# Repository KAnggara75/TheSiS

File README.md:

# TheSiS

My TheSiS for Bachelor Degree

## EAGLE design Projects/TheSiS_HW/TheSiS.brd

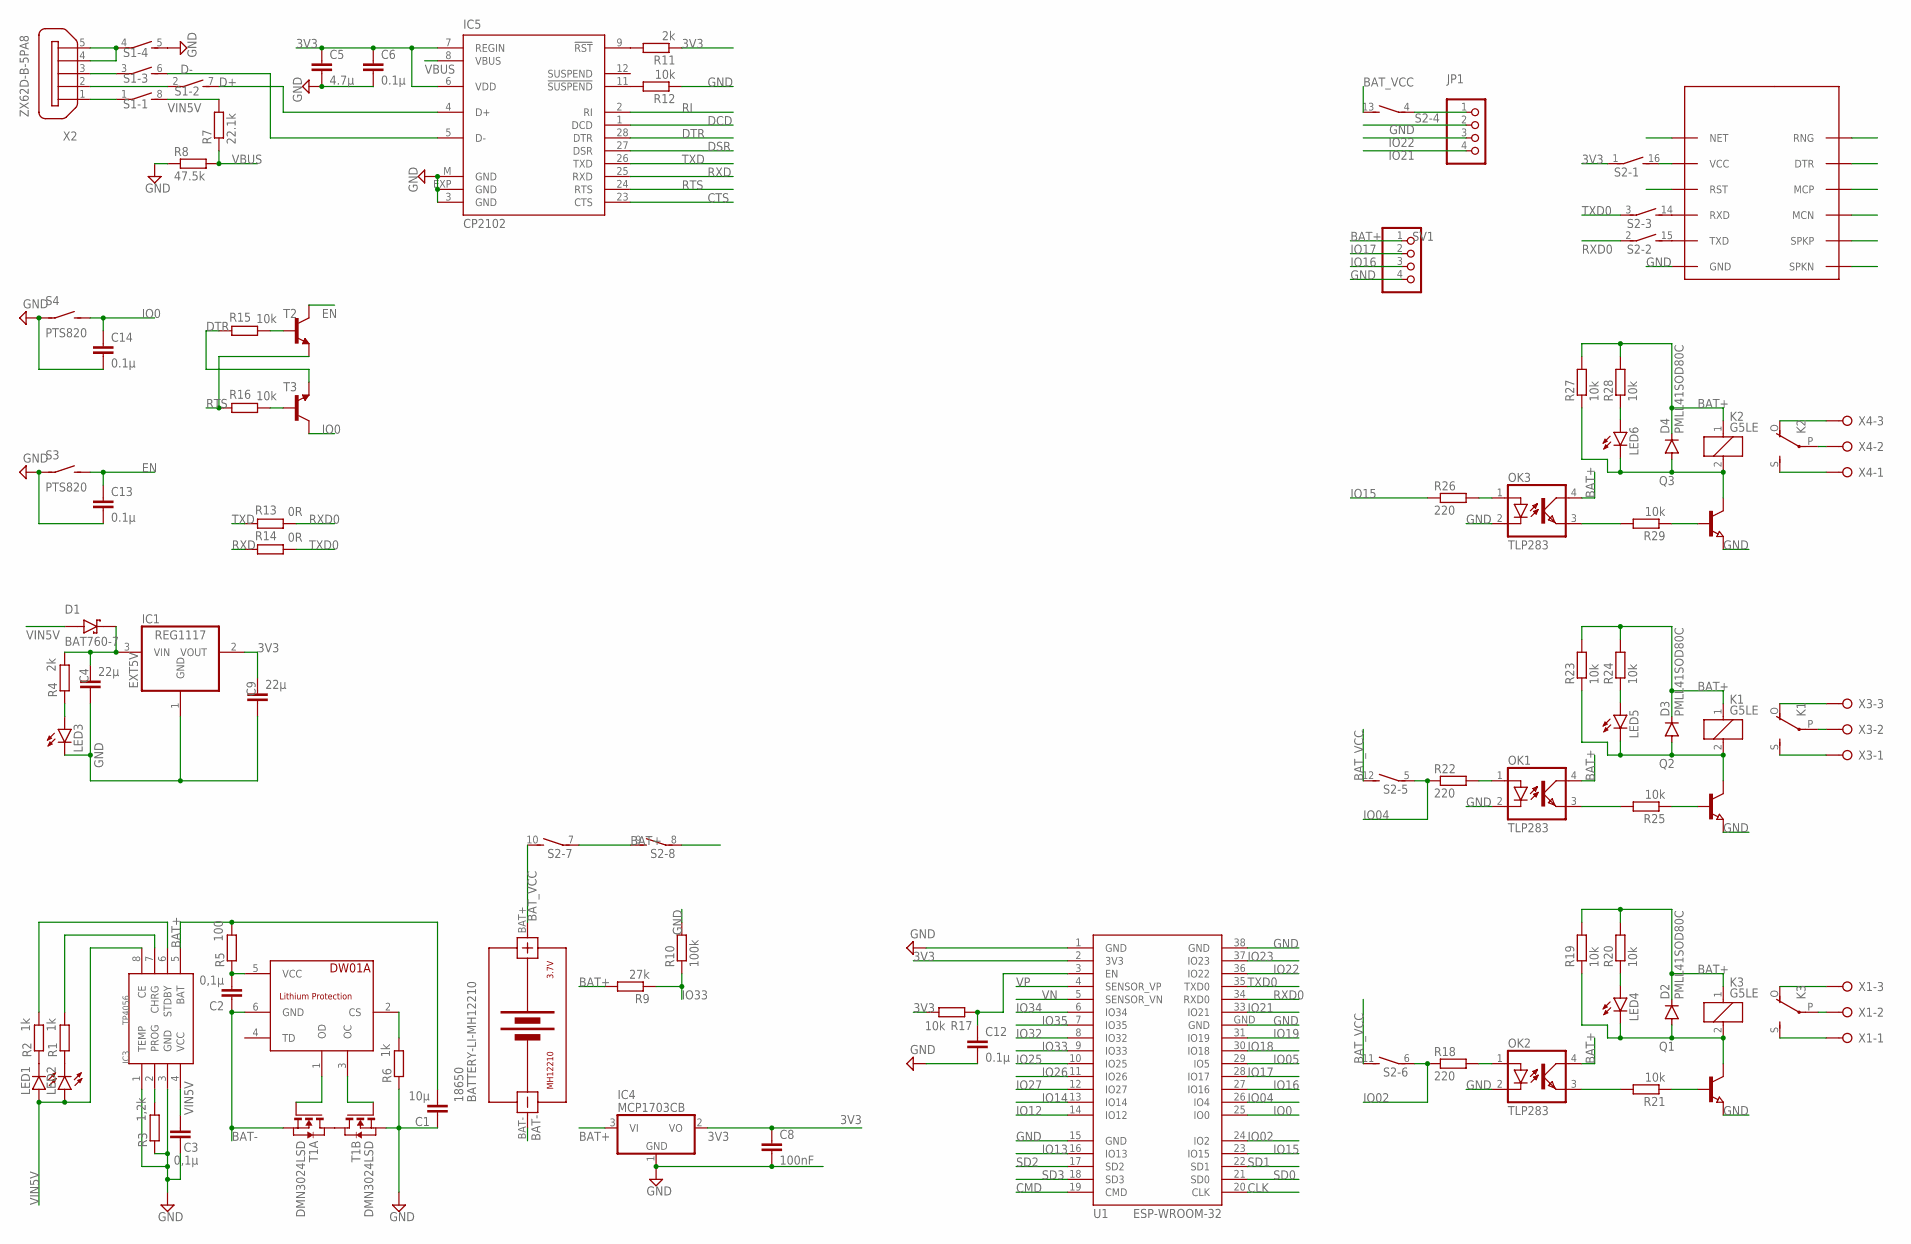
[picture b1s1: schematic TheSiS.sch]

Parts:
18650: BATTERY-LI-MH12210
C1: 10µ; C0603
C2: 0,1µ; C0805
C3: 0,1µ; C0805K
C4, C9: 22µ; C0805
C5: 4.7µ; C0805
C6, C12, C13, C14: 0.1µ; C0805
C8: 100nF; C0805
D1: BAT760-7; SOD2513X120N
D2, D3, D4: PMLL41SOD80C; SOD80C
IC1: REG1117; SOT223A
IC3: TP4056; SOP-8
IC4: MCP1703CB; SOT23
IC5: CP2102; QFN28
JP1: PINHD-1X4; 1X04
K1, K2, K3: G5LE
LED1, LED2, LED3, LED4, LED5, LED6: LEDCHIP-LED0805; CHIP-LED0805
OK1, OK2, OK3: TLP283; SOT23-4
Q1, Q2, Q3: NPN-TRANSISTOR_SOT23; SOT23
R1, R2, R6: 1k; R0603
R3: 1,2k; R0603
R4, R11: 2k; R0805
R5: 100; R0603
R7: 22.1k; R0805
R8: 47.5k; R0805
R9: 27k; R0805
R10: 100k; R0805
R12, R15, R16, R17, R19, R20, R21, R23, R24, R25, R27, R28, R29: 10k; R0805
R13, R14: 0R; R0805
R18, R22, R26: 220; R0805
S1: DIP04S
S2: DIP08S
S3, S4: PTS820
SV1: PINHD-1X4; 1X04
T1: DMN3024LSD; TSSOP-8
T2, T3: -NPN-SOT23-EBC; SOT23-EBC
U1: ESP-WROOM-32
U$1: DW01A; SOT23-6
U$4: SIM800L; SIM-CORE
X1, X3, X4: W237-03P; W237-3
X2: ZX62D-B-5PA8

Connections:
3V3: C5.1, C6.1, C8.1, C9.1, IC1.2 (VOUT), IC4.2 (VO), IC5.6 (VDD), IC5.7 (REGIN), R11.1, R17.2, S2.1, U1.2 (3V3)
$VCCSIM800: S2.16 (2), U$4.VCC
BAT+: C1.2, D2.C, D3.C, D4.C, IC3.5 (BAT), IC4.3 (VI), K1.1, K2.1, K3.1, OK1.4 (COL), OK2.4 (COL), OK3.4 (COL), R5.2, R9.2, R19.2, R20.2, R23.2, R24.2, R27.2, R28.2, S2.8 (1), SV1.1
BAT-: 18650.BAT-, C2.1, T1.2 (S), T1.3 (S), U$1.6 (GND)
BAT_VCC: 18650.BAT+, S2.10 (2), S2.11 (2), S2.12 (2), S2.13 (2)
CLK: U1.20 (CLK)
CMD: U1.19 (CMD)
CTS: IC5.23 (CTS)
D+: IC5.4 (D+), S1.7 (2)
D-: IC5.5 (D-), S1.6 (2)
DCD: IC5.1 (DCD)
DSR: IC5.27 (DSR)
DTR: IC5.28 (DTR), R15.2, T3.E
EN: C13.1, S3.2 (S), T2.C
EXT5V: C4.1, D1.C (K), IC1.3 (VIN), R4.2
GND: C1.1, C3.1, C4.2, C5.2, C6.2, C8.2, C9.2, C12.2, C13.2, C14.2, IC1.1 (GND), IC3.1 (TEMP), IC3.3 (GND), IC4.1 (GND), IC5.3 (GND), IC5.EXP (GND), IC5.M (GND), JP1.2, LED3.C, OK1.2 (C), OK2.2 (C), OK3.2 (C), Q1.2 (E), Q2.2 (E), Q3.2 (E), R3.1, R6.1, R8.1, R10.2, R12.1, S1.5 (2), S3.1, S4.1, SV1.4, T1.6 (S), T1.7 (S), U1.1 (GND), U1.15 (GND), U1.38 (GND), U1.GND, U$4.GND
IO0: C14.1, S4.2 (S), T3.C, U1.25 (IO0)
IO02: R18.1, S2.6 (1), U1.24 (IO2)
IO04: R22.1, S2.5 (1), U1.26 (IO4)
IO05: U1.29 (IO5)
IO12: U1.14 (IO12)
IO13: U1.16 (IO13)
IO14: U1.13 (IO14)
IO15: R26.1, U1.23 (IO15)
IO16: SV1.3, U1.27 (IO16)
IO17: SV1.2, U1.28 (IO17)
IO18: U1.30 (IO18)
IO19: U1.31 (IO19)
IO21: JP1.4, U1.33 (IO21)
IO22: JP1.3, U1.36 (IO22)
IO23: U1.37 (IO23)
IO25: U1.10 (IO25)
IO26: U1.11 (IO26)
IO27: U1.12 (IO27)
IO32: U1.8 (IO32)
IO33: R9.1, R10.1, U1.9 (IO33)
IO34: U1.6 (IO34)
IO35: U1.7 (IO35)
unnamed: T1.1 (D), T1.8 (D)
unnamed: IC3.2 (PROG), R3.2
unnamed: IC3.6 (STDBY), R2.2
unnamed: IC3.7 (CHRG), R1.2
unnamed: R6.2, U$1.2 (CS)
unnamed: LED1.C, R2.1
unnamed: LED2.C, R1.1
unnamed: T1.4 (G), U$1.1 (OD)
unnamed: T1.5 (G), U$1.3 (OC)
unnamed: LED3.A, R4.1
unnamed: C2.2, R5.1, U$1.5 (VCC)
unnamed: S1.1, X2.1
unnamed: IC5.9 (!RST), R11.2
unnamed: IC5.11 (!SUSPEND), R12.2
unnamed: S1.4 (1), X2.4, X2.5
unnamed: S1.2 (1), X2.2
unnamed: S1.3 (1), X2.3
unnamed: R15.1, T2.B
unnamed: R16.1, T3.B
unnamed: C12.1, R17.1, U1.3 (EN)
unnamed: S2.7 (1), S2.9 (2)
unnamed: S2.15 (2), U$4.TXD
unnamed: S2.14 (2), U$4.RXD
unnamed: OK2.1 (A), R18.2
unnamed: OK2.3 (EMIT), R21.2
unnamed: JP1.1, S2.4 (1)
unnamed: Q1.1 (B), R21.1
unnamed: OK3.1 (A), R26.2
unnamed: OK3.3 (EMIT), R29.2
unnamed: Q3.1 (B), R29.1
unnamed: D2.A, K3.2, LED4.C, Q1.3 (C), R19.1
unnamed: K3.O, X1.3
unnamed: K3.P, X1.2
unnamed: K3.S, X1.1
unnamed: LED4.A, R20.1
unnamed: OK1.1 (A), R22.2
unnamed: OK1.3 (EMIT), R25.2
unnamed: Q2.1 (B), R25.1
unnamed: D3.A, K1.2, LED5.C, Q2.3 (C), R23.1
unnamed: LED5.A, R24.1
unnamed: K1.O, X3.3
unnamed: K1.P, X3.2
unnamed: K1.S, X3.1
unnamed: D4.A, K2.2, LED6.C, Q3.3 (C), R27.1
unnamed: LED6.A, R28.1
unnamed: K2.O, X4.3
unnamed: K2.P, X4.2
unnamed: K2.S, X4.1
RI: IC5.2 (RI)
RTS: IC5.24 (RTS), R16.2, T2.E
RXD: IC5.25 (RXD), R14.2
RXD0: R13.1, S2.2 (1), U1.34 (RXD0)
SD0: U1.21 (SD0)
SD1: U1.22 (SD1)
SD2: U1.17 (SD2)
SD3: U1.18 (SD3)
TXD: IC5.26 (TXD), R13.2
TXD0: R14.1, S2.3 (1), U1.35 (TXD0)
VBUS: IC5.8 (VBUS), R7.1, R8.2
VIN5V: C3.2, D1.A, IC3.4 (VCC), IC3.8 (CE), LED1.A, LED2.A, R7.2, S1.8 (2)
VN: U1.5 (SENSOR_VN)
VP: U1.4 (SENSOR_VP)

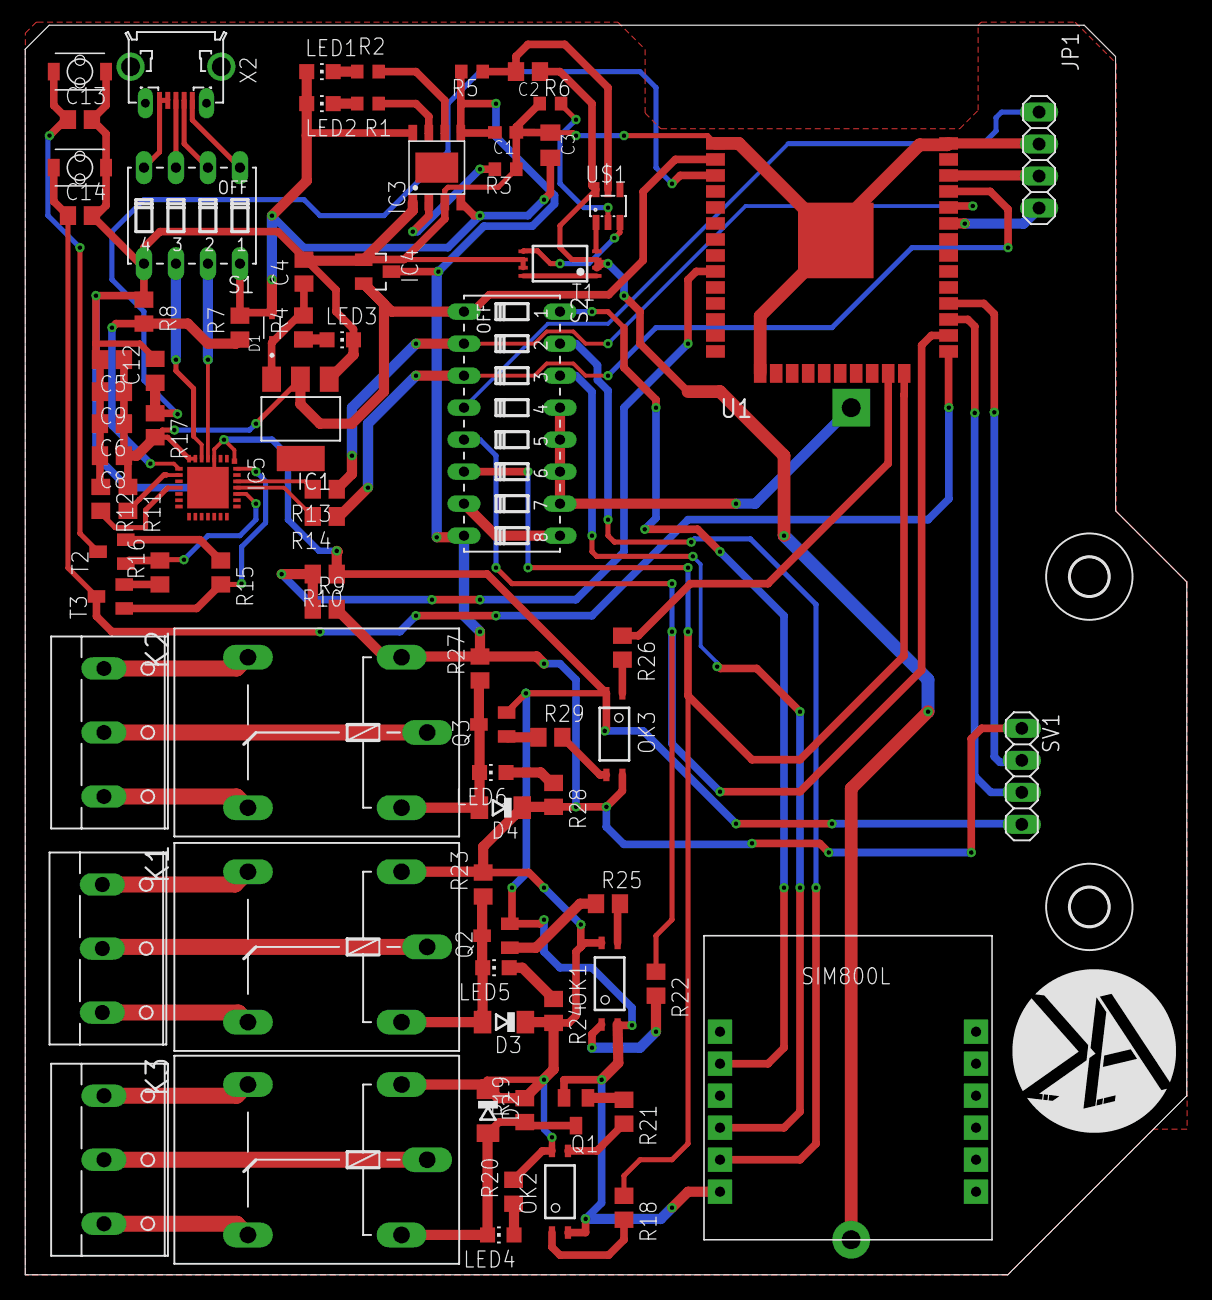
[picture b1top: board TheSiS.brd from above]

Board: 2 copper layers, 92.2 x 99.2 mm, 82 parts (1 on the bottom side), 75 nets.

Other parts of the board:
U$2, U$3: 3,0

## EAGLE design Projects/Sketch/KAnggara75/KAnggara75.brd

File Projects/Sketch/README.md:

A6-ESP8266-breakout
===================

This is a breakout board that includes an ESP8266 and an integrated A6 module.
It is best used with the [A6 ESP8266
library](https://github.com/skorokithakis/A6lib).

It is still incomplete, and looks like this:

## Schematic

## Board

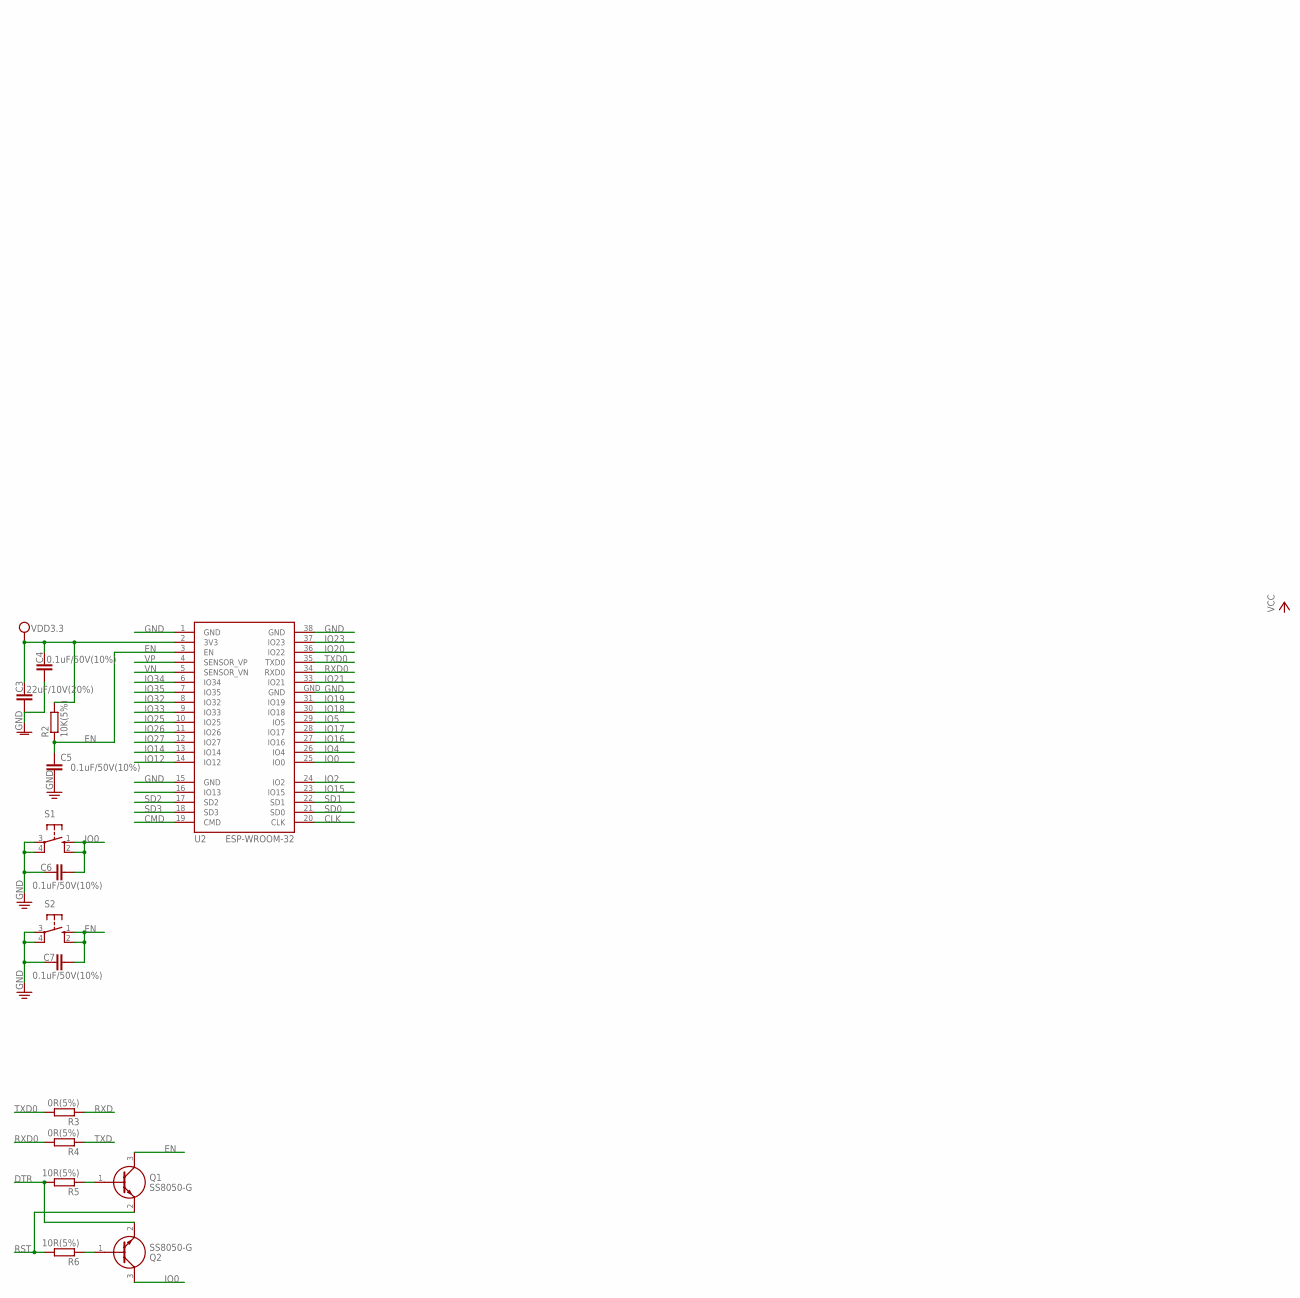
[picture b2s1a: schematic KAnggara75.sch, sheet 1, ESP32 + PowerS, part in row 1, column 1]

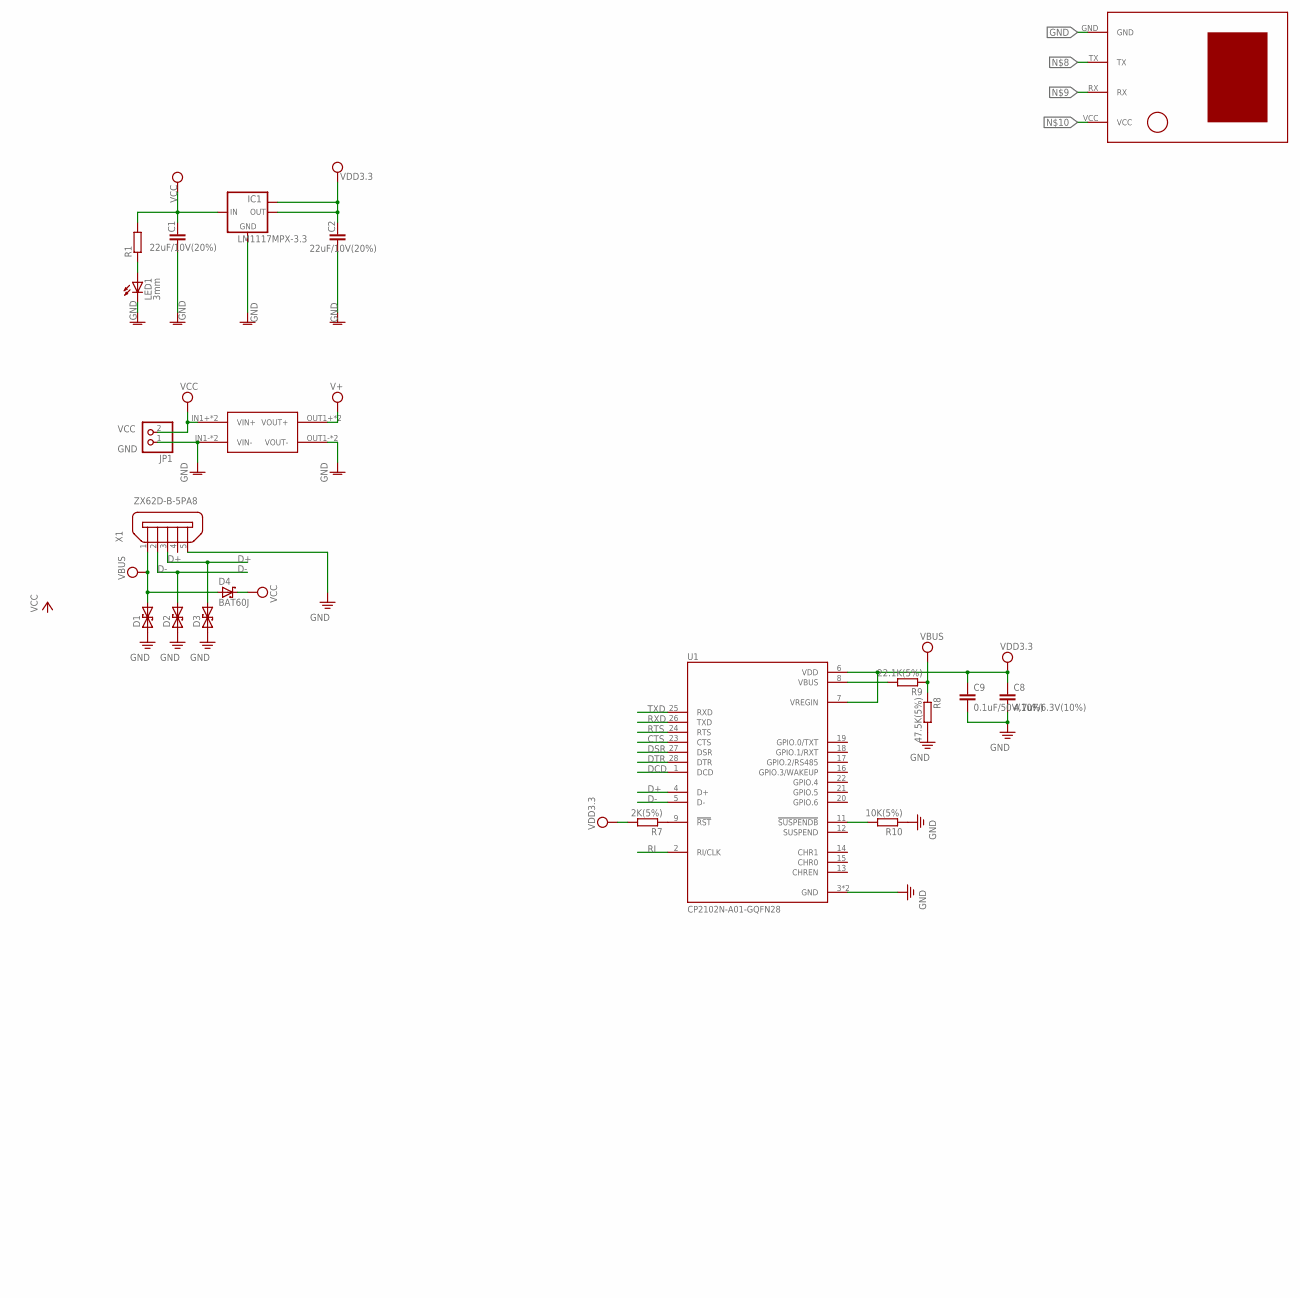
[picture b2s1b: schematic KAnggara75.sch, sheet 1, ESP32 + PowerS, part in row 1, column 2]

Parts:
C1, C2, C3: 22uF/10V(20%); C1206
C4, C5, C6, C7, C9: 0.1uF/50V(10%); C1206
C8: 4.7uF/6.3V(10%); C1206
D1, D2, D3: DIODE_SCHOTTKY2-P2-15; P2-15
D4: BAT60J; SOD323_ST
IC1: LM1117MPX-3.3; SOT223
JP1: PINHD-1X2; 1X02
LED1: 3mm; LED3MM
Q1, Q2: SS8050-G; SOT95P240X115-3N
R1: R-EU_R1210; R1210
R2, R10: 10K(5%); R1210
R3, R4: 0R(5%); R1210
R5, R6: 10R(5%); R1210
R7: 2K(5%); R1210
R8: 47.5K(5%); R1210
R9: 22.1K(5%); R1210
S1, S2: 10-XX; B3F-10XX
U1: CP2102N-A01-GQFN28; QFN50P500X500X80-29N
U2: ESP-WROOM-32
U$1: MP1584; DC-BRICK
U$3: U-BLOX-NEO6V2
X1: ZX62D-B-5PA8

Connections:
CLK: U2.20 (CLK)
CMD: U2.19 (CMD)
CTS: U1.23 (CTS)
D+: D3.C (2), U1.4 (D+), X1.3; also elsewhere on the board
D-: D2.C (2), U1.5 (D-), X1.2; also elsewhere on the board
DCD: U1.1 (DCD)
DSR: U1.27 (DSR)
DTR: Q2.2 (E), R5.2, U1.28 (DTR)
EN: C5.1, C7.1, Q1.3 (C), R2.1, S2.1 (S), S2.2 (S1), U2.3 (EN)
GND: C1.2, C2.2, C3.2, C4.2, IC1.1 (GND), JP1.1, LED1.K (C), U2.1 (GND), U2.15 (GND), U2.38 (GND), U2.GND, U$1.IN1- (VIN-), U$1.IN2- (VIN-), U$1.OUT1- (VOUT-), U$1.OUT2- (VOUT-), U$3.GND
IO0: C6.1, Q2.3 (C), S1.1 (S), S1.2 (S1), U2.25 (IO0)
IO2: U2.24 (IO2)
IO4: U2.26 (IO4)
IO5: U2.29 (IO5)
IO12: U2.14 (IO12)
IO14: U2.13 (IO14)
IO15: U2.23 (IO15)
IO16: U2.27 (IO16)
IO17: U2.28 (IO17)
IO18: U2.30 (IO18)
IO19: U2.31 (IO19)
IO20: U2.36 (IO22)
IO21: U2.33 (IO21)
IO23: U2.37 (IO23)
IO25: U2.10 (IO25)
IO26: U2.11 (IO26)
IO27: U2.12 (IO27)
IO32: U2.8 (IO32)
IO33: U2.9 (IO33)
IO34: U2.6 (IO34)
IO35: U2.7 (IO35)
unnamed: LED1.A, R1.1
unnamed: R7.1, U1.9 (!RST)
unnamed: R9.2, U1.8 (VBUS)
unnamed: Q2.1 (B), R6.1
unnamed: Q1.1 (B), R5.1
unnamed: R10.2, U1.11 (!SUSPENDB)
PE: C5.2, C6.2, C7.2, C8.2, C9.2, D1.A (1), D2.A (1), D3.A (1), R8.2, R10.1, S1.3, S1.4 (P1), S2.3, S2.4 (P1), U1.3 (GND), U1.29 (GND), X1.5; also elsewhere on the board
RI: U1.2 (RI/CLK)
RST: Q1.2 (E), R6.2
RTS: U1.24 (RTS)
RXD: R3.1, U1.26 (TXD)
RXD0: R4.2, U2.34 (RXD0)
SD0: U2.21 (SD0)
SD1: U2.22 (SD1)
SD2: U2.17 (SD2)
SD3: U2.18 (SD3)
TXD: R4.1, U1.25 (RXD)
TXD0: R3.2, U2.35 (TXD0)
VCC: C1.1, D4.C, IC1.3 (IN), JP1.2, R1.2, U$1.IN1+ (VIN+), U$1.IN2+ (VIN+); also elsewhere on the board
VDD: C2.1, C3.1, C4.1, C8.1, C9.1, IC1.2 (OUT), IC1.TAB (OUT1), R2.2, R7.2, R8.1, R9.1, U1.6 (VDD), U1.7 (VREGIN), U2.2 (3V3)
VEE: D1.C (2), D4.A, U$1.OUT1+ (VOUT+), U$1.OUT2+ (VOUT+), X1.1; also elsewhere on the board
VN: U2.5 (SENSOR_VN)
VP: U2.4 (SENSOR_VP)

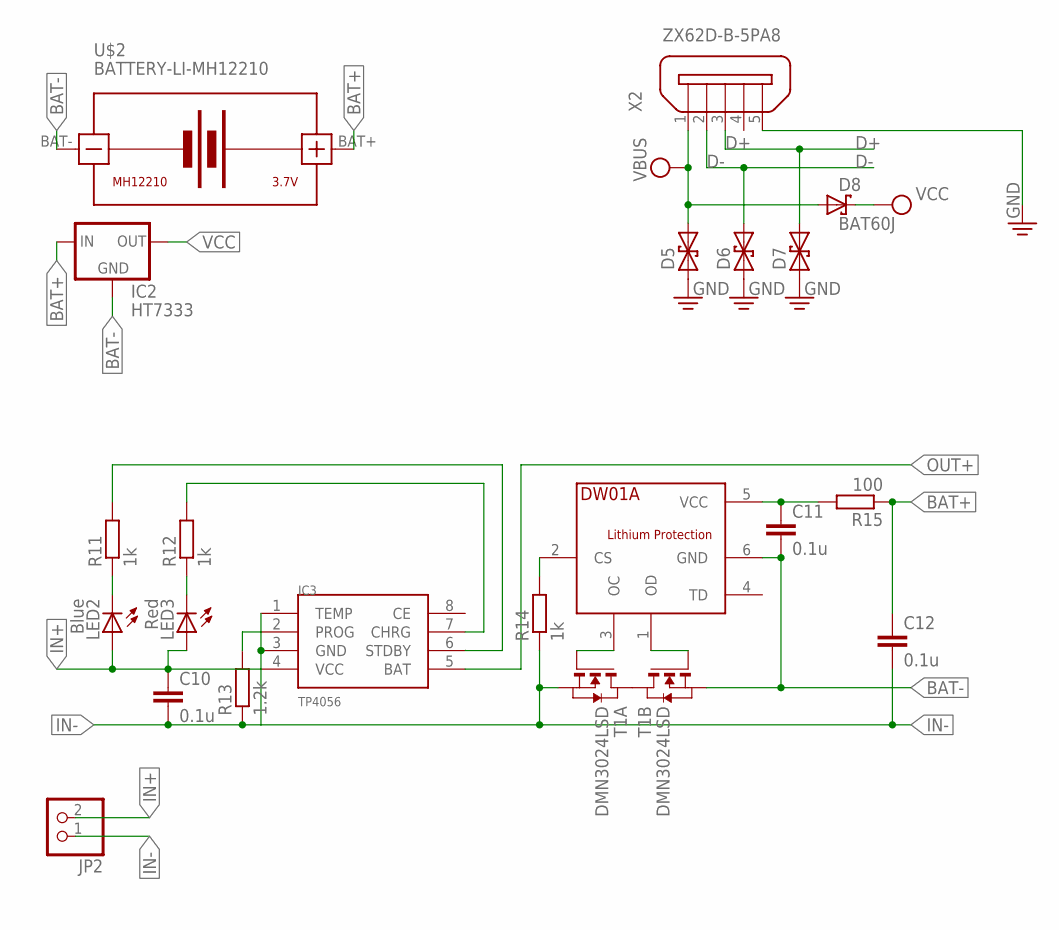
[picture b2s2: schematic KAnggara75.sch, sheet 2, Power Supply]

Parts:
C10, C11, C12: 0.1u; C0805
D5, D6, D7: DIODE_SCHOTTKY2-P2-15; P2-15
D8: BAT60J; SOD323_ST
IC2: HT7333; SOT-89
IC3: TP4056; SOP-8
JP2: PINHD-1X2; 1X02
LED2: Blue; 1206
LED3: Red; 1206
R11, R12, R14: 1k; R0805
R13: 1.2k; R0805
R15: 100; R0805
T1: DMN3024LSD; TSSOP-8
U$2: BATTERY-LI-MH12210
U$5: DW01A; SOT23-6
X2: ZX62D-B-5PA8

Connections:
BAT+: C12.1, IC2.3 (IN), IC2.4 (IN), R15.1, U$2.BAT+
BAT-: C11.2, IC2.2 (GND), T1.6 (S), T1.7 (S), U$2.BAT-, U$5.6 (GND)
D+: D7.C (2), X2.3; also elsewhere on the board
D-: D6.C (2), X2.2; also elsewhere on the board
IN+: C10.1, IC3.4 (VCC), JP2.2, LED2.A, LED3.A
IN-: C10.2, C12.2, IC3.1 (TEMP), IC3.3 (GND), JP2.1, R13.1, R14.1, T1.2 (S), T1.3 (S)
unnamed: LED2.C, R11.1
unnamed: LED3.C, R12.1
unnamed: IC3.6 (STDBY), R11.2
unnamed: IC3.7 (CHRG), R12.2
unnamed: T1.1 (D), T1.8 (D)
unnamed: T1.4 (G), U$5.3 (OC)
unnamed: T1.5 (G), U$5.1 (OD)
unnamed: IC3.2 (PROG), R13.2
unnamed: R14.2, U$5.2 (CS)
unnamed: C11.1, R15.2, U$5.5 (VCC)
OUT+: IC3.5 (BAT)
PE: D5.A (1), D6.A (1), D7.A (1), X2.5; also elsewhere on the board
VCC: D8.C, IC2.1 (OUT); also elsewhere on the board
VEE: D5.C (2), D8.A, X2.1; also elsewhere on the board

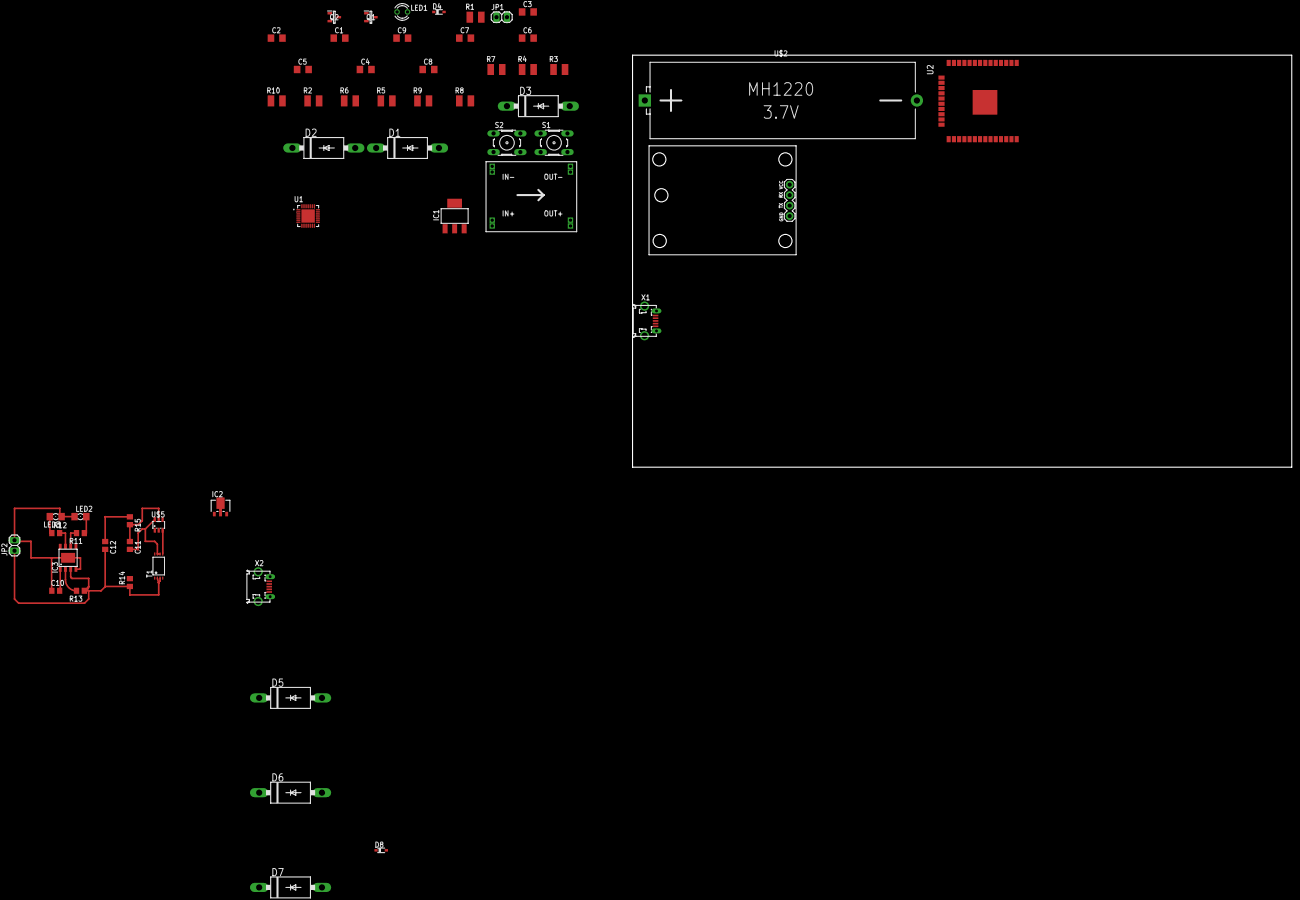
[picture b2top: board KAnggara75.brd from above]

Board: 2 copper layers, 160.0 x 100.0 mm, 56 parts (0 on the bottom side), 35 nets.

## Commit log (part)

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2019-12-19 Modifikasi Readme Mark Down
2019-12-22 Update 23 Desember 2019 (Menambah Video & Sketch Eagle)
2019-12-23 Add ESP-IDT
2019-12-23 Add IDF DIr
2019-12-25 Menghapus IDF
2020-01-01 Update 1 Januari 2020
2020-01-01 Menambakan gambar Tampilan Aplikasi
2020-01-01 Merubah Dir TheSis_App menjadi TheSiS_App pada Project
2020-01-02 Add new Screen Shoot
2020-01-02 Update Screen Shoot
2020-01-03 Add Logo & Title image file for pcb
2020-01-06 Make Folder Project ESP32
2020-01-17 Add Administratif
2020-03-23 Update 24 Maret 2020 (Menamahkan LaTex)
2020-03-23 Update LaTeX
2020-03-24 Menambahkan file Jurnal dan BAB I kedalam Proposal.docx
2020-03-24 Menghapus output LaTeX
2020-03-24 menambah ukuran huruf pada proposal.tex
2020-04-05 administratif
2020-04-05 memasukan laporan promin
2020-04-05 update proposal dan workspace
2020-04-09 menambahkan surat penajuan pembimbing
2020-04-09 memperbaharui borang 1
2020-04-09 update proposal bab 1 menjadi 4 paragraf
2020-04-10 Menambahkan Jurnal
2020-04-10 update Proposal, menambahkan pararaf terakhir bab i, Penelitian terkait
2020-04-10 Menyelesaikan Latar Belakang
2020-04-10 Membuat Halaman i menhadi I-1 pada Bab I
2020-04-10 Menyelessaikan BAB I, perbaiki halaman Romawi
2020-04-15 memulai BAB II
2020-04-17 Menambahkan 2 paragraf terakhir pada BAB I
2020-04-21 Menambahkan 9 jurnal dari IEEE
2020-04-21 Ganti judul + menghapus paragraf 2
2020-04-22 Membuat Praktikum Kosentrasi Komputer
2020-04-22 Menambah BAB II 2.1. Studi Literatur
2020-04-23 Memperbaharui Rumusan Masalah
2020-05-01 + Datasheet ESP32
2020-05-01 Laporan Promin Terbaru Fix
2020-05-01 Menambahkan Mikrokontroler esp32 pada bab 2
2020-05-04 Form B2 Bukti Bebas Praktikum
2020-05-13 Menambah temlate artikel Sitekin
2020-05-13 Gambar power skema ESP32
2020-05-13 Merubah kata Extensa menjadi Xtensa, Menambahkan sub bab µP
2020-05-13 Menambahkan prosesor 2.2.1. Xtensa LX6
2020-05-13 Menambahkan uC
2020-05-13 datasheet dan gambar up
2020-05-19 Gambar ESP32
2020-05-19 Jurnal Post-RISC
2020-05-19 Update 19 Mei 2020
2020-05-19 Menambahkan Gamar SIM800L
2020-05-19 Menyelesaikan Sub Bab SIM800L
2020-05-20 Menambah file gambar
2020-05-20 Menyelesaikan SIM800L, GPS, Akselerometer dan modul relay (SUB BAB)
2020-05-21 Menyelesaikan Sub Bab Dataase
2020-05-21 + Logo Android 2019
2020-05-21 Menyelesaikan sub bab android
2020-05-26 Memulai BAB III
2020-05-26 Menambah File Flowchart
2020-05-26 Membuat case 3D
2020-05-28 git Ignore Poster & stensa.pdf
2020-05-29 Tambah Gambar
2020-05-29 Menghapus file blok siagram pada folder project/sketch/kanggara75
2020-05-29 Perbaiki gambar flowchart hardware
2020-05-29 Update file flowchart
2020-05-29 ++ Ilustrasi sistem
2020-05-29 menmbah gambar dengan resolusi yg lebih rendah
2020-05-29 memperkecil resolusi gambar
2020-05-29 memperkecik resolusi gambar => memperkecil file size
2020-05-31 Finishing, tinggal daftar isi dkk
2020-05-31 Sebelum editing Italic
2020-05-31 Upload classroom *Finish*
2020-06-01 revisi 0.1
2020-06-01 mengubah judul sub bab 3.8
2020-06-01 Mengubah Sub Judul 3.8
2020-06-07 Revisi 08 Juni 2020 1. Merubah sub bab 3.8. menjadi Skenario Pengujian 2. Menambah Gambar halaman utama aplikasi 3. Menambah Referensi Skripsi (Tahun 2017 & 2019) 4. Menggabungkan poin poin pada rumu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
2020-06-10 Menambahkan Java. Proposal.docx
2020-06-15 Menyelesaikan Borang 1
2020-06-15 step ke borang 2
2020-06-15 Progres Untuk Borang 2 (TTD bimingan dan penunjukan pembimbing)
2020-06-25 TTD Borang 2
2020-06-25 Menyelesaikan Borang 2
2020-06-25 Menyelesaikan Pra Seminar
2020-06-25 Memasukan KHS dan Transkrip Kedalam Folder
2020-06-25 Memasukan Penunjukan Pembimbing Kedalam Folder Yg lama DImasukan Dalam file.rar
2020-06-25 Rar File Borang 1
2020-06-25 Penunjukan Penguji Selesai
2020-06-25 Update Flowchart
2020-07-21 borang 2 post seminar
2020-07-21 Borang Hasil Seminar
2020-07-21 Menghapus Jurnal Artikel Sitekin
2020-07-21 Revisi 21.07.2001
2020-07-21 Revisi 21.07.2002 (Smart Early System)
2020-07-24 Selesai Revisi Penguji Taap 1 (24.07.2001)
2020-07-24 Gambar + Flowchart + Jurnal
2020-08-20 21.08.2001 (Selesai Seminar + Berita Acara)
2020-08-23 Menghapus file tidak penting
2020-08-23 Template Jurnal JOIN
2020-08-23 menghapus latex
2020-09-30 update template jurnal
2020-09-30 Add Manajemant Waktu
2020-09-30 add JST Template v2
2020-09-30 Selesai Mikro....
2020-10-03 Rename Jurnal dkk to Reference
2020-10-03 sama seperti sebelumnya
2020-10-03 Arsipkan Folder Borang_01
2020-10-03 menghapus folder borang 2
2020-10-03 arsipkan file setelah seminar
2020-10-03 arsipkan folder pra seminar
2020-10-03 menambahkan undangan dan penunjukan pembombing dalam folder jilid 1
2020-10-03 menambahkan File logo baru
2020-10-03 meindahkan SKBB
2020-10-03 skematik untuk power supply
2020-10-03 Add database untuk thesis web
2020-10-03 rename folder 3d => thesis _3d
2020-10-03 Rename HW_Design => Thesis_HW
2020-10-03 remove unused file [041020]
2020-10-15 Add TheSiS_bot [Telegram Bot]
2020-10-18 Pending/Cancel Telegram Bot
2020-10-18 Accel Push POST_HTTP
2020-10-20 Finish TheSiS_HW Schematic
2020-10-21 Selesai Board v20.10.21
2020-10-21 Menamahkan Logo
2020-10-21 Finish Hardware v20.10.21
2020-10-22 Image Board Final v20.10.22
2020-10-22 Garber File v20.10.22
2020-10-22 Finish Board v20.10.20 [Order PCBWay.com]
2020-10-28 Menghapus Jurnal JOIN
2020-11-05 Perbaiki typo
2020-11-05 Sebelum install November 2020
2020-12-04 Update .gitignore and Update sql file for thesis_web project
2021-02-13 Mulai Jurnal 2021
2021-02-14 menambahkan jurnal pengukuran gps
2021-02-14 update 14 Februari 2021
2021-03-25 Update 25 Maret 2021
2021-03-30 compress file size of jurnal out
2021-03-30 Menambahkan gambar uji coba
2021-03-30 add Jurnal ref
2021-03-30 add ino file
2021-03-30 Add Jurnal Output file
2021-05-08 menambahkan hasil review
2021-06-04 menambahkan jurnal baru
2021-06-04 Update Revisi 1
2021-06-05 memindahkan contoh jurnal ke folde refrennsi
2021-06-05 Hasil Revisi ronde 2
2021-06-05 revisi 05 Juni 2021 [sitasi - belum selesai]
2021-06-12 perbaiki sitasi
2021-06-12 menyelesaikan abstrak
2021-06-14 update Simpulan 14 Juni 2021
2021-06-14 revisi hasil dan pembahasan 14 juni 2021
2022-04-15 init App
2022-04-15 init Api
2022-04-15 fix: Api folder
2022-04-21 app: init
2022-04-30 add: CODEUWSERS
2022-05-01 add: Splash with BLoC
2022-05-07 add: login from bloc
2022-05-07 add: CI/CD for app
2022-05-07 fix: git action checkout repo from v1 to v2
2022-05-07 fix: git action flutter from v2.4 to v2
2022-05-07 fix: desktop depedency protocol from git to https
2022-05-07 fix: pubspec.yaml version
2022-05-07 0.1.3 Release
2022-05-07 fix: app sign
2022-05-07 add: 0.1.5
2022-05-07 fix: gragle var
2022-05-16 Upgrade to Flutter 3
2022-06-03 upgrade laravel to 9.16.x
2022-06-03 fix: move api to standalone repo
2022-06-03 fix: move api to standalone repoi submodule
2022-06-03 fix: conditional CI/CD
2022-06-03 fix: #web folder
2022-06-03 #web deploy test1
2022-06-03 fix: remove submodule
2022-06-03 test: deploy #web
2022-06-03 test: deploy #web 2
2022-06-03 fix: web deploy server folder #web 2
2022-06-03 add: write .env file in CD
2022-06-03 #Web Deploy
2022-06-04 build(deps): bump async from 2.6.3 to 2.6.4 in /api
    Bumps [async](https://github.com/caolan/async) from 2.6.3 to 2.6.4.
    - [Release notes](https://github.com/caolan/async/releases)
    - [Changelog](https://github.com/caolan/async/blob/v2.6.4/CHANGELOG.md)
    - [Commits](https://github.com/caolan/async/compare/v2.6.3...v2.6.4)
    ---
    updated-dependencies:
2022-06-04 build(deps-dev): bump postcss from 8.4.12 to 8.4.14 in /api
    Bumps [postcss](https://github.com/postcss/postcss) from 8.4.12 to 8.4.14.
    - [Release notes](https://github.com/postcss/postcss/releases)
    - [Changelog](https://github.com/postcss/postcss/blob/main/CHANGELOG.md)
    - [Commits](https://github.com/postcss/postcss/compare/8.4.12...8.4.14)
    ---
    updated-dependencies:
2022-06-04 build(deps-dev): bump tailwindcss from 3.0.23 to 3.0.24 in /api
    Bumps [tailwindcss](https://github.com/tailwindlabs/tailwindcss) from 3.0.23 to 3.0.24.
    - [Release notes](https://github.com/tailwindlabs/tailwindcss/releases)
    - [Changelog](https://github.com/tailwindlabs/tailwindcss/blob/master/CHANGELOG.md)
    - [Commits](https://github.com/tailwindlabs/tailwindcss/compare/v3.0.23...v3.0.24)
    ---
    updated-dependencies:
2022-06-04 build(deps-dev): bump axios from 0.25.0 to 0.27.2 in /api
    Bumps [axios](https://github.com/axios/axios) from 0.25.0 to 0.27.2.
    - [Release notes](https://github.com/axios/axios/releases)
    - [Changelog](https://github.com/axios/axios/blob/v0.27.2/CHANGELOG.md)
    - [Commits](https://github.com/axios/axios/compare/v0.25.0...v0.27.2)
    ---
    updated-dependencies:
2022-06-04 build(deps-dev): bump autoprefixer from 10.4.4 to 10.4.7 in /api
    Bumps [autoprefixer](https://github.com/postcss/autoprefixer) from 10.4.4 to 10.4.7.
    - [Release notes](https://github.com/postcss/autoprefixer/releases)
    - [Changelog](https://github.com/postcss/autoprefixer/blob/main/CHANGELOG.md)
    - [Commits](https://github.com/postcss/autoprefixer/compare/10.4.4...10.4.7)
    ---
    updated-dependencies:
2022-06-04 build(deps-dev): bump laravel-mix from 6.0.43 to 6.0.46 in /api
    Bumps [laravel-mix](https://github.com/JeffreyWay/laravel-mix) from 6.0.43 to 6.0.46.
    - [Release notes](https://github.com/JeffreyWay/laravel-mix/releases)
    - [Changelog](https://github.com/laravel-mix/laravel-mix/blob/master/CHANGELOG.md)
    - [Commits](https://github.com/JeffreyWay/laravel-mix/commits)
    ---
    updated-dependencies:
2022-06-04 add: api end point
2022-06-04 fix: CODEOWNER
2022-06-04 fix: flutter widget test condition
2022-06-04 fix: git action
2022-06-05 add: api migration => finish
2022-06-06 add: API for login and board
2022-06-10 build(deps): bump guzzlehttp/guzzle from 7.4.3 to 7.4.4 in /api
    Bumps [guzzlehttp/guzzle](https://github.com/guzzle/guzzle) from 7.4.3 to 7.4.4.
    - [Release notes](https://github.com/guzzle/guzzle/releases)
    - [Changelog](https://github.com/guzzle/guzzle/blob/master/CHANGELOG.md)
    - [Commits](https://github.com/guzzle/guzzle/compare/7.4.3...7.4.4)
    ---
    updated-dependencies:
2022-06-25 add: app prepare to release
2022-06-25 fix: api #web
2022-06-25 add: docs
2022-06-25 build(deps): bump guzzlehttp/guzzle from 7.4.3 to 7.4.5 in /api
    Bumps [guzzlehttp/guzzle](https://github.com/guzzle/guzzle) from 7.4.3 to 7.4.5.
    - [Release notes](https://github.com/guzzle/guzzle/releases)
    - [Changelog](https://github.com/guzzle/guzzle/blob/master/CHANGELOG.md)
    - [Commits](https://github.com/guzzle/guzzle/compare/7.4.3...7.4.5)
    ---
    updated-dependencies:
2022-06-25 fix: update #web
2022-06-25 add: meter to km if d > 1000
2022-06-28 add: KRS
2022-06-28 add: docs for administratif
2022-07-15 add: gitignore
2022-07-20 add: bebas pustaka
2022-09-22 [ImgBot] Optimize images
    *Total -- 4,091.08kb -> 3,758.58kb (8.13%)
    /app/flutter_01.png -- 3.36kb -> 0.88kb (73.7%)
    /app/assets/icons/marker.svg -- 9.22kb -> 3.80kb (58.8%)
    /app/web/icons/Icon-maskable-512.png -- 20.51kb -> 10.54kb (48.61%)
    /app/web/icons/Icon-maskable-192.png -- 5.46kb -> 3.66kb (33.05%)
    /app/macos/Runner/Assets.xcassets/AppIcon.appiconset/app_icon_512.png -- 14.45kb -> 9.69kb (32.93%)
2022-11-28 lulus yey
2023-02-01 build(deps): bump symfony/http-kernel from 6.0.9 to 6.0.20 in /api
    Bumps [symfony/http-kernel](https://github.com/symfony/http-kernel) from 6.0.9 to 6.0.20.
    - [Release notes](https://github.com/symfony/http-kernel/releases)
    - [Changelog](https://github.com/symfony/http-kernel/blob/6.2/CHANGELOG.md)
    - [Commits](https://github.com/symfony/http-kernel/compare/v6.0.9...v6.0.20)
    ---
    updated-dependencies:

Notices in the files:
parts and their libraries:
esp32: Creative Commons Attribution-ShareAlike 4.0 International
diy-modules: Released under the Creative Commons Attribution 4.0 International License: http://creativecommons.org/licenses/by/4.0
